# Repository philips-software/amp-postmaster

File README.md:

# Postmaster (Programmer Of ST Microcontrollers Attached to ST Experiment boaRds)

<!-- markdownlint-disable -->

<!-- markdownlint enable -->

## Overview

Postmaster is a device that clicks on top of an STM32 Nucleo-F767ZI board from ST Microelectronics, and through its Ethernet connector you can program the Nucleo and communicate with it.

In this way, Postmaster is usable in hardware-in-the-loop tests, where a test board is reachable through the internet. That test board can first be programmed with the correct firmware. For communicating with the test board, a client can connect to Postmaster via a websocket connection, and talk to the attached board either via a plain UART connection, or via an [ECHO](https://philips-software.github.io/amp-embedded-infra-lib/embedded_infrastructure_library/7.0.0/Echo.html) connection. This communication line is used to execute tests.

Test boards enabled by Postmaster are intended to be inherently scalable; Adding tests boards in a setup should be as simple as putting a Postmaster on top of it, configuring the Postmaster with a few labels describing the characteristics of that board, and connecting it to the internet. A locally installed proxy (also part of this archive) provides discoverability of all Postmasters in its vicinity, and routes incoming requests for boards with certain characteristics to any available board.

By providing a schematics and PCB layout, the Postmaster firmware, and various tools, this repository aims to provide a full suite of components tackling all aspects of connecting a hardware-in-the-loop test board to the cloud.

Requirements of Postmaster are documented [here](Documents/Requirements.md).

## Community

This project uses the [CODE_OF_CONDUCT](./CODE_OF_CONDUCT.md) to define expected conduct in our community. Instances of abusive, harassing, or otherwise unacceptable behavior may be reported by contacting a project [CODEOWNER](.github/CODEOWNERS)

## Changelog

See [CHANGELOG](./CHANGELOG.md) for more info on what's been changed.

## Build

The Postmaster binaries can be built by executing the following commands:

```shell
cmake --preset stm32f407
cmake --build --preset stm32f407-MinSizeRel
```

The postmaster.flex utility can be build by executing the following commands:

```shell
cmake --preset host
cmake --build --preset host-RelWithDebInfo
```

## Reporting vulnerabilities

If you find a vulnerability, please report it to us!
See [security](.github/SECURITY.md) for more information.

## Licenses

See [LICENSE](./LICENSE.md)

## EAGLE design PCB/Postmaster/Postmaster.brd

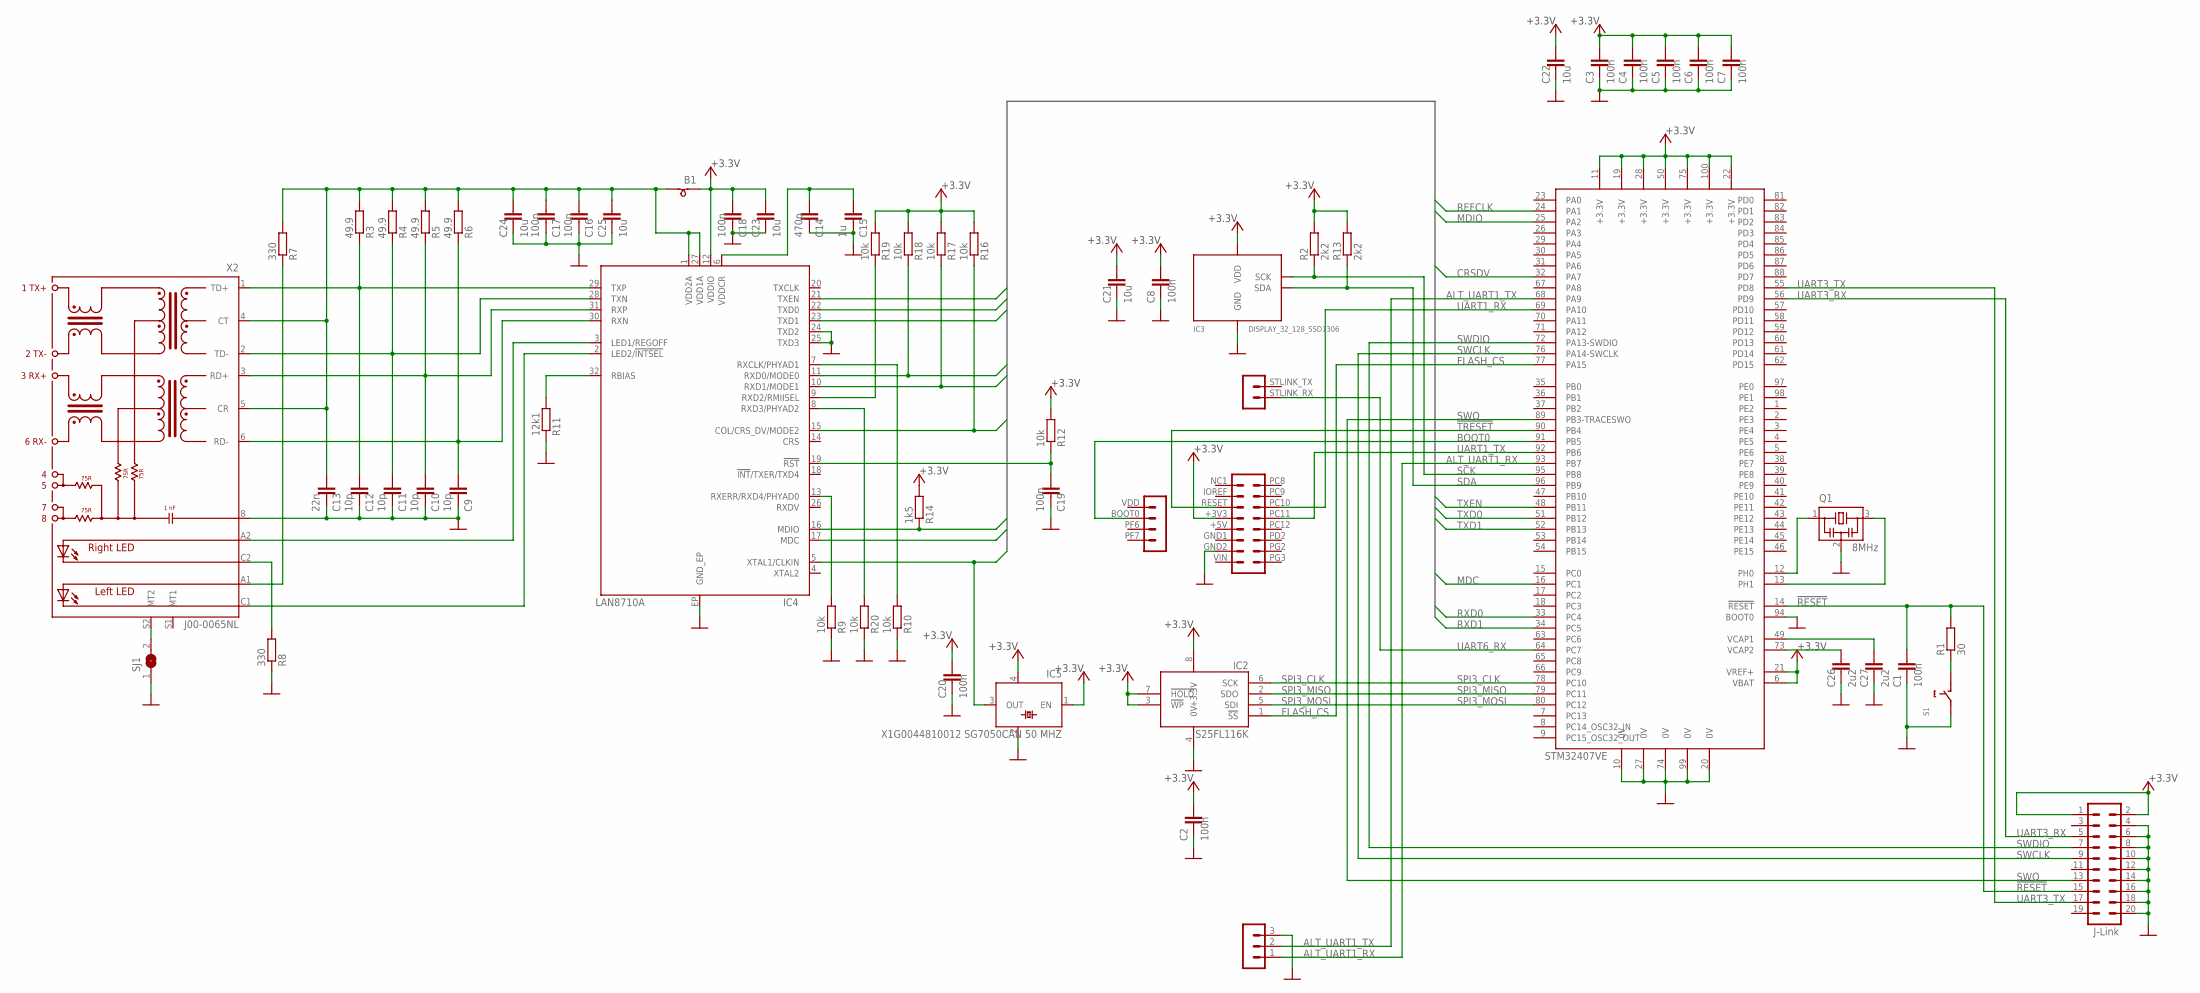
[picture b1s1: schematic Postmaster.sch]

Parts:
B1: BEADSMD; 0805
C1, C2, C3, C4, C5, C6, C7, C8, C16, C17, C18, C19, C20: 100n; 0805
C9, C10, C11, C12: 10p; 0805
C13: 22n; 0805
C14: 470p; 0805
C15: 1u; 0805
C21, C22, C23, C24, C25: 10u; 0805
C26, C27: 2u2; 0805
IC1: STM32F407; TQFP100
IC2: S25FL116K; SOIC8-WIDE
IC3: DISPLAY_32_128_SSD1306; DISPLAY_128_32_SSD1306
IC4: LAN8710A; QFN32
IC5: X1G0044810012 SG7050CAN 50 MHZ; SM77H
Q1: 8MHz; RESONATOR-SMALL
R1: 30; 0805
R2, R13: 2k2; 0805
R3, R4, R5, R6: 49.9; 0805
R7, R8: 330; 0805
R9, R10, R12, R16, R17, R18, R19, R20: 10k; 0805
R11: 12k1; 0805
R14: 1k5; 0805
S1: SWITCHSMD; SWITCH-SMD
SJ1: SJ
U$1: NUCLEO-TOPLEFT
U$3: HEADER-MALE-3
X1: HEADER-IDC-10-2; IDC-10_2
X2: J00-0065NL; ETHERNET

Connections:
0V: C1.2, C2.2, C3.2, C4.2, C5.2, C6.2, C7.2, C8.2, C9.2, C10.2, C11.2, C12.2, C13.2, C14.2, C15.2, C16.2, C17.2, C18.2, C19.2, C20.2, C21.2, C22.2, C23.2, C24.2, C25.2, C26.2, C27.2, IC1.10 (0V), IC1.20 (0V), IC1.27 (0V), IC1.74 (0V), IC1.94 (BOOT0), IC1.99 (0V), IC2.4 (0V), IC3.GND, IC4.24 (TXD2), IC4.25 (TXD3), IC4.EP (GND_EP), IC5.2 (0V), Q1.2, R8.1, R9.1, R10.1, R11.1, R20.1, S1.3 (2), S1.4 (2), SJ1.1, U$1.GND2 (13), U$3.3, X1.4, X1.6, X1.8, X1.10, X1.12, X1.14, X1.16, X1.18, X1.20, X2.8
!RESET!: C1.1, IC1.14 (!RESET!), R1.2, X1.15
!TRESET!: IC1.90 (PB4), U$1.RESET (5)
+3.3V: B1.1, C2.1, C3.1, C4.1, C5.1, C6.1, C7.1, C8.1, C18.1, C20.1, C21.1, C22.1, C23.1, IC1.6 (VBAT), IC1.11 (+3.3V), IC1.19 (+3.3V), IC1.21 (VREF+), IC1.22 (+3.3V), IC1.28 (+3.3V), IC1.50 (+3.3V), IC1.75 (+3.3V), IC1.100 (+3.3V), IC2.3 (!WP!), IC2.7 (!HOLD!), IC2.8 (+3.3V), IC3.VCC (VDD), IC4.12 (VDDIO), IC5.1 (EN), IC5.4 (+3.3V), R2.2, R12.2, R13.2, R14.2, R16.2, R17.2, R18.2, R19.2, U$1.+3V3 (7), X1.1, X1.2
ALT_UART1_RX: IC1.93 (PB7), U$3.1
ALT_UART1_TX: IC1.68 (PA9), U$3.2
BOOT0: IC1.91 (PB5), U$1.BOOT0 (2)
CRSDV: IC1.32 (PA7), IC4.15 (COL/CRS_DV/MODE2), R16.1
FLASH_CS: IC1.77 (PA15), IC2.1 (!SS!)
MDC: IC1.16 (PC1), IC4.17 (MDC)
MDIO: IC1.25 (PA2), IC4.16 (MDIO), R14.1
unnamed: C26.1, IC1.73 (VCAP2)
unnamed: R1.1, S1.1, S1.2 (1)
unnamed: C27.1, IC1.49 (VCAP1)
unnamed: R7.1, X2.A1 (A-L)
unnamed: IC4.3 (LED1/REGOFF), X2.A2 (A-R)
unnamed: R8.2, X2.C2 (C-R)
unnamed: IC1.12 (PH0), Q1.1
unnamed: IC1.13 (PH1), Q1.3
unnamed: C12.1, IC4.29 (TXP), R3.1, X2.1 (TD+)
unnamed: C11.1, IC4.28 (TXN), R4.1, X2.2 (TD-)
unnamed: C10.1, IC4.31 (RXP), R5.1, X2.3 (RD+)
unnamed: C9.1, IC4.30 (RXN), R6.1, X2.6 (RD-)
unnamed: IC4.2 (LED2/!INTSEL!), X2.C1 (C-L)
unnamed: IC4.13 (RXERR/RXD4/PHYAD0), R9.2
unnamed: IC4.7 (RXCLK/PHYAD1), R10.2
unnamed: IC4.32 (RBIAS), R11.2
unnamed: C14.1, C15.1, IC4.6 (VDDCR)
unnamed: SJ1.2, X2.S2 (MT2)
unnamed: B1.2, C13.1, C16.1, C17.1, C24.1, C25.1, IC4.1 (VDD2A), IC4.27 (VDD1A), R3.2, R4.2, R5.2, R6.2, R7.2, X2.4 (CT), X2.5 (CR)
unnamed: C19.1, IC4.19 (!RST!), R12.1
unnamed: IC4.8 (RXD3/PHYAD2), R20.2
unnamed: IC4.9 (RXD2/RMIISEL), R19.1
REFCLK: IC1.24 (PA1), IC4.5 (XTAL1/CLKIN), IC5.3 (OUT)
RXD0: IC1.33 (PC4), IC4.11 (RXD0/MODE0), R18.1
RXD1: IC1.34 (PC5), IC4.10 (RXD1/MODE1), R17.1
SCK: IC1.95 (PB8), IC3.SCK, R2.1
SDA: IC1.96 (PB9), IC3.SDA, R13.1
SPI3_CLK: IC1.78 (PC10), IC2.6 (SCK)
SPI3_MISO: IC1.79 (PC11), IC2.2 (SDO)
SPI3_MOSI: IC1.80 (PC12), IC2.5 (SDI)
SWCLK: IC1.76 (PA14-SWCLK), X1.9
SWDIO: IC1.72 (PA13-SWDIO), X1.7
SWO: IC1.89 (PB3-TRACESWO), X1.13
TXD0: IC1.51 (PB12), IC4.22 (TXD0)
TXD1: IC1.52 (PB13), IC4.23 (TXD1)
TXEN: IC1.48 (PB11), IC4.21 (TXEN)
UART1_RX: IC1.69 (PA10), U$1.PC10 (6)
UART1_TX: IC1.92 (PB6), U$1.PC11 (8)
UART3_RX: IC1.56 (PD9), X1.5
UART3_TX: IC1.55 (PD8), X1.17
UART6_RX: IC1.64 (PC7), U$1.STLINK_RX (1)

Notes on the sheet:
J-Link
STM32407VE

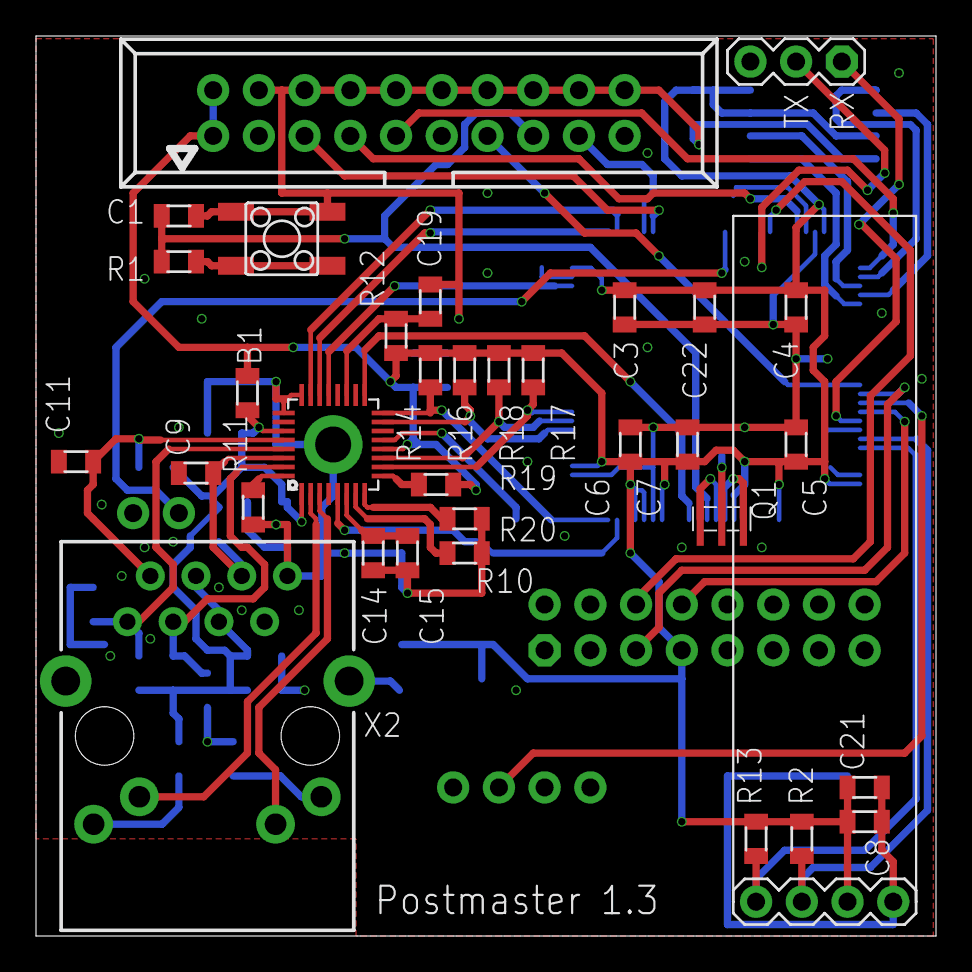
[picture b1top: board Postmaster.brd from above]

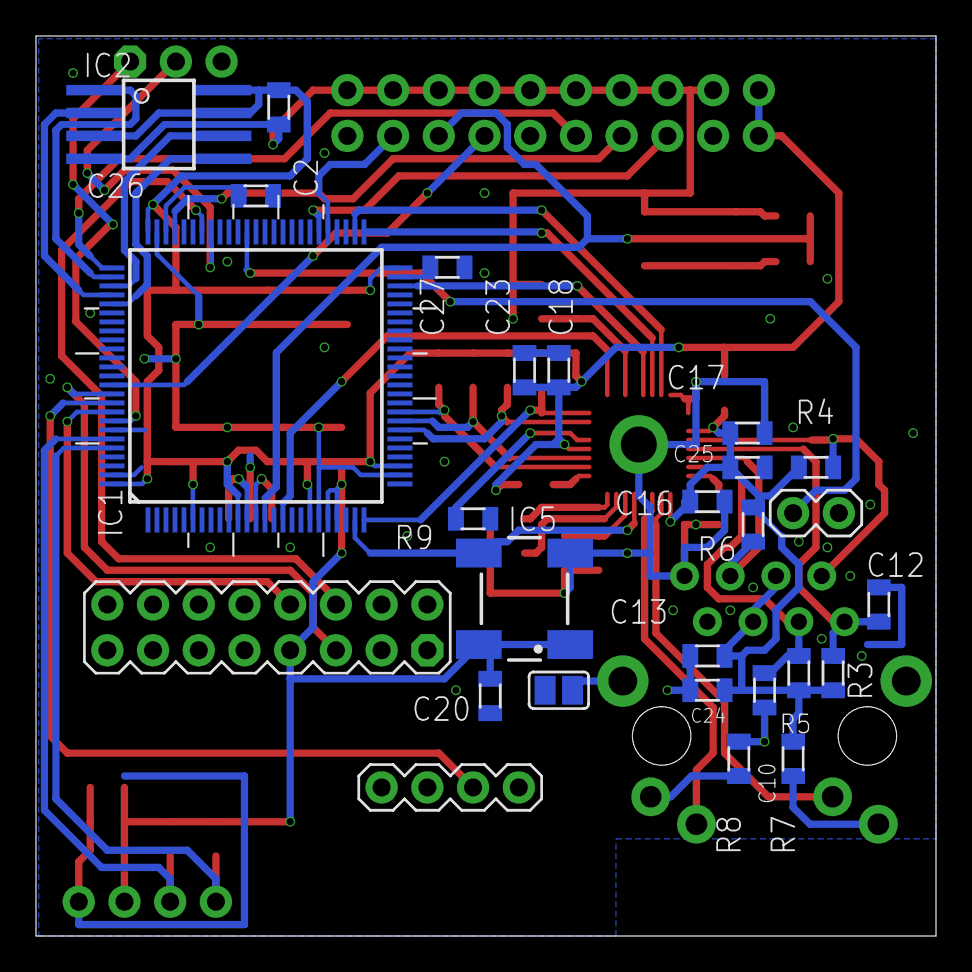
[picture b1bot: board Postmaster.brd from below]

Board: 2 copper layers, 50.0 x 50.0 mm, 59 parts (25 on the bottom side), 52 nets.

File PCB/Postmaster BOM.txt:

Partlist exported from C:/Dev/Postmaster/PCB/Postmaster/Postmaster.sch at 17/04/2022 20:07:00

Part Value                          Device                 Package                Description                
B1   BEADSMD                        BEADSMD                0805                                              
C1   100n                           CAPACITOR0805          0805                                              
C2   100n                           CAPACITOR0805          0805                                              
C3   100n                           CAPACITOR0805          0805                                              
C4   100n                           CAPACITOR0805          0805                                              
C5   100n                           CAPACITOR0805          0805                                              
C6   100n                           CAPACITOR0805          0805                                              
C7   100n                           CAPACITOR0805          0805                                              
C8   100n                           CAPACITOR0805          0805                                              
C9   10p                            CAPACITOR0805          0805                                              
C10  10p                            CAPACITOR0805          0805                                              
C11  10p                            CAPACITOR0805          0805                                              
C12  10p                            CAPACITOR0805          0805                                              
C13  22n                            CAPACITOR0805          0805                                              
C14  470p                           CAPACITOR0805          0805                                              
C15  1u                             CAPACITOR0805          0805                                              
C16  100n                           CAPACITOR0805          0805                                              
C17  100n                           CAPACITOR0805          0805                                              
C18  100n                           CAPACITOR0805          0805                                              
C19  100n                           CAPACITOR0805          0805                                              
C20  100n                           CAPACITOR0805          0805                                              
C21  10u                            CAPACITOR0805          0805                                              
C22  10u                            CAPACITOR0805          0805                                              
C23  10u                            CAPACITOR0805          0805                                              
C24  10u                            CAPACITOR0805          0805                                              
C25  10u                            CAPACITOR0805          0805                                              
C26  2u2                            CAPACITOR0805          0805                                              
C27  2u2                            CAPACITOR0805          0805                                              
IC1  STM32F407                      STM32F407              TQFP100                                           
IC2  S25FL116K                      S25FL116KW             SOIC8-WIDE                                        
IC3  DISPLAY_32_128_SSD1306         DISPLAY_32_128_SSD1306 DISPLAY_128_32_SSD1306                            
IC4  LAN8710A                       LAN8710A               QFN32                                             
IC5  X1G0044810012 SG7050CAN 50 MHZ SM77H                  SM77H                  3.3V CMOS Clock Oscillator 
Q1   8MHz                           RESONATOR-S            RESONATOR-SMALL                                   
R1   30                             RESISTORR0805          0805                                              
R2   2k2                            RESISTORR0805          0805                                              
R3   49.9                           RESISTORR0805          0805                                              
R4   49.9                           RESISTORR0805          0805                                              
R5   49.9                           RESISTORR0805          0805                                              
R6   49.9                           RESISTORR0805          0805                                              
R7   330                            RESISTORR0805          0805                                              
R8   330                            RESISTORR0805          0805                                              
R9   10k                            RESISTORR0805          0805                                              
R10  10k                            RESISTORR0805          0805                                              
R11  12k1                           RESISTORR0805          0805                                              
R12  10k                            RESISTORR0805          0805                                              
R13  2k2                            RESISTORR0805          0805                                              
R14  1k5                            RESISTORR0805          0805                                              
R16  10k                            RESISTORR0805          0805                                              
R17  10k                            RESISTORR0805          0805                                              
R18  10k                            RESISTORR0805          0805                                              
R19  10k                            RESISTORR0805          0805                                              
R20  10k                            RESISTORR0805          0805                                              
S1   SWITCHSMD                      SWITCHSMD              SWITCH-SMD                                        
SJ1                                 SJ                     SJ                     SMD solder JUMPER          
U$1  NUCLEO-TOPLEFT                 NUCLEO-TOPLEFT         NUCLEO-TOPLEFT                                    
X1   HEADER-IDC-10-2                HEADER-IDC-10-2        IDC-10_2                                          
X2   J00-0065NL                     J00-0065NL             ETHERNET

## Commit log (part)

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2024-12-04 Update submodules
2024-12-04 ci: validate pull request titles
2024-12-06 feat(deps): bump the git-submodules group with 2 updates
    Bumps the git-submodules group with 2 updates: [amp-embedded-infra-lib](https://github.com/philips-software/amp-embedded-infra-lib) and [amp-hal-st](https://github.com/philips-software/amp-hal-st).
    Updates `amp-embedded-infra-lib` from `6c84af5` to `c77731b`
    - [Release notes](https://github.com/philips-software/amp-embedded-infra-lib/releases)
    - [Commits](https://github.com/philips-software/amp-embedded-infra-lib/compare/6c84af5324c79219059d1066cc5ce3aad8f2b927...c77731ba79bfbe8af22450cf33fcdf4fd30a3587)
    Updates `amp-hal-st` from `1529067` to `f11d3bf`
    - [Release notes](https://github.com/philips-software/amp-hal-st/releases)
2024-12-19 postmaster/flex/Main: Fix reading from environment
2025-01-10 feat(deps): bump the git-submodules group across 1 directory with 3 updates
    Bumps the git-submodules group with 3 updates in the / directory: [amp-embedded-infra-lib](https://github.com/philips-software/amp-embedded-infra-lib), [amp-hal-st](https://github.com/philips-softwar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
    Updates `amp-embedded-infra-lib` from `6c84af5` to `ae01eea`
    - [Release notes](https://github.com/philips-software/amp-embedded-infra-lib/releases)
    - [Commits](https://github.com/philips-software/amp-embedded-infra-lib/compare/6c84af5324c79219059d1066cc5ce3aad8f2b927...ae01eeae459647a0f8a52430bb26740d47b2945e)
    Updates `amp-hal-st` from `1
2025-01-19 Accept multiple connections on port 80, one connection on port 8080
2025-01-31 build(deps): bump the github-actions group across 1 directory with 6 updates
    Bumps the github-actions group with 6 updates in the / directory:
    | Package | From | To |
    | --- | --- | --- |
    | [hendrikmuhs/ccache-action](https://github.com/hendrikmuhs/ccache-action) | `1.2.14` | `1.2.16` |
    | [oxsecurity/megalinter](https://github.com/oxsecurity/megalinter) | `8.3.0` | `8.4.1` |
    | [actions/upload-artifact](https://github.com/actions/upload-artifact) | `4.5.0` | `4.6.0` |
2025-02-13 build(deps): bump philips-software/amp-devcontainer-cpp
    Bumps [philips-software/amp-devcontainer-cpp](https://github.com/philips-software/amp-devcontainer) from v5.6.0 to v5.6.1.
    - [Release notes](https://github.com/philips-software/amp-devcontainer/releases)
    - [Changelog](https://github.com/philips-software/amp-devcontainer/blob/main/CHANGELOG.md)
    - [Commits](https://github.com/philips-software/amp-devcontainer/compare/v5.6.0...v5.6.1)
    ---
    updated-dependencies:
2025-02-20 feat: add kicad design for Postmaster (#51)
    * feat: redo the schematics and board in KiCad
    * Update schematics
    * Update schematics
    * Update schematics
    * Update schematics
    * Update schematics, add production files
2025-03-03 feat(deps): bump the git-submodules group across 1 directory with 3 updates
    Bumps the git-submodules group with 3 updates in the / directory: [amp-embedded-infra-lib](https://github.com/philips-software/amp-embedded-infra-lib), [amp-hal-st](https://github.com/philips-softwar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
    Updates `amp-embedded-infra-lib` from `6c84af5` to `eccbab6`
    - [Release notes](https://github.com/philips-software/amp-embedded-infra-lib/releases)
    - [Commits](https://github.com/philips-software/amp-embedded-infra-lib/compare/6c84af5324c79219059d1066cc5ce3aad8f2b927...eccbab6e47da83929395a27b047a695ecd29e7a6)
    Updates `amp-hal-st` from `1
2025-03-24 build(deps): bump the github-actions group across 1 directory with 6 updates
    Bumps the github-actions group with 6 updates in the / directory:
    | Package | From | To |
    | --- | --- | --- |
    | [actions/cache](https://github.com/actions/cache) | `4.2.1` | `4.2.3` |
    | [oxsecurity/megalinter](https://github.com/oxsecurity/megalinter) | `8.4.2` | `8.5.0` |
    | [actions/upload-artifact](https://github.com/actions/upload-artifact) | `4.6.0` | `4.6.2` |
2025-04-25 build(deps): bump philips-software/amp-devcontainer-cpp
    Bumps [philips-software/amp-devcontainer-cpp](https://github.com/philips-software/amp-devcontainer) from v5.6.2 to v6.0.1.
    - [Release notes](https://github.com/philips-software/amp-devcontainer/releases)
    - [Changelog](https://github.com/philips-software/amp-devcontainer/blob/main/CHANGELOG.md)
    - [Commits](https://github.com/philips-software/amp-devcontainer/compare/v5.6.2...v6.0.1)
    ---
    updated-dependencies:
2025-05-08 build(deps): bump oxsecurity/megalinter in the github-actions group (#78)
    Bumps the github-actions group with 1 update: [oxsecurity/megalinter](https://github.com/oxsecurity/megalinter).
    Updates `oxsecurity/megalinter` from 8.6.0 to 8.7.0
    - [Release notes](https://github.com/oxsecurity/megalinter/releases)
    - [Changelog](https://github.com/oxsecurity/megalinter/blob/main/CHANGELOG.md)
    - [Commits](https://github.com/oxsecurity/megalinter/compare/04cf22b980c2e9c2121553417ed651c944afc8e1...5a91fb06c83d0e69fbd23756d47438aa723b4a5a)
    ---
2025-05-21 chore(deps): bump philips-software/amp-devcontainer-cpp
    Bumps [philips-software/amp-devcontainer-cpp](https://github.com/philips-software/amp-devcontainer) from v6.0.1 to v6.0.2.
    - [Release notes](https://github.com/philips-software/amp-devcontainer/releases)
    - [Changelog](https://github.com/philips-software/amp-devcontainer/blob/main/CHANGELOG.md)
    - [Commits](https://github.com/philips-software/amp-devcontainer/compare/v6.0.1...v6.0.2)
    ---
    updated-dependencies:
2025-05-22 fix: align flash writes to 16 bytes (#80)
    * fix: align flash writes to 16 bytes
    * Wait for flash initialization done
    * FlexHttpClient: Move attaching of websocket
    * FirmwareReceptorResetTarget: Use timers instead of HAL_Delay
    * Set starting
    * Update container
2025-06-16 chore(deps): bump the github-actions group across 1 directory with 6 updates
    Bumps the github-actions group with 6 updates in the / directory:
    | Package | From | To |
    | --- | --- | --- |
    | [actions/checkout](https://github.com/actions/checkout) | `4.1.7` | `4.2.2` |
    | [docker/metadata-action](https://github.com/docker/metadata-action) | `5.5.1` | `5.7.0` |
    | [docker/setup-buildx-action](https://github.com/docker/setup-buildx-action) | `3.6.1` | `3.10.0` |
2025-08-08 chore(deps): bump the github-actions group across 1 directory with 4 updates (#98)
    Bumps the github-actions group with 4 updates in the / directory: [actions/cache](https://github.com/actions/cache), [docker/metadata-action](https://github.com/docker/metadata-action), [docker/login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
    Updates `actions/cache` from 4.2.3 to 4.2.4
    - [Release notes](https://github.com/actions/cache/releases)
    - [Changelog](https://github.com/actions/cache/blob/main/RELEASES.md)
    - [Commits](https://github.com/actions/cache/compare/5a3ec84eff668545956fd18022155c47e9
2025-09-10 chore(deps): bump philips-software/amp-devcontainer-cpp
    Bumps [philips-software/amp-devcontainer-cpp](https://github.com/philips-software/amp-devcontainer) from 6.2.1 to 6.3.0.
    - [Release notes](https://github.com/philips-software/amp-devcontainer/releases)
    - [Changelog](https://github.com/philips-software/amp-devcontainer/blob/main/CHANGELOG.md)
    - [Commits](https://github.com/philips-software/amp-devcontainer/compare/v6.2.1...v6.3.0)
    ---
    updated-dependencies:
2025-10-08 chore(deps): bump philips-software/amp-devcontainer-cpp (#114)
    Bumps [philips-software/amp-devcontainer-cpp](https://github.com/philips-software/amp-devcontainer) from 6.2.1 to v6.5.0.
    - [Release notes](https://github.com/philips-software/amp-devcontainer/releases)
    - [Changelog](https://github.com/philips-software/amp-devcontainer/blob/main/CHANGELOG.md)
    - [Commits](https://github.com/philips-software/amp-devcontainer/compare/v6.2.1...v6.5.0)
    ---
    updated-dependencies:
2025-10-23 chore: enable usb passthrough debugging (#119)
2025-10-27 feat(deps): bump the git-submodules group across 1 directory with 3 updates
    Bumps the git-submodules group with 3 updates in the / directory: [amp-embedded-infra-lib](https://github.com/philips-software/amp-embedded-infra-lib), [amp-hal-st](https://github.com/philips-softwar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
    Updates `amp-embedded-infra-lib` from `9d3718f` to `2c26042`
    - [Release notes](https://github.com/philips-software/amp-embedded-infra-lib/releases)
    - [Commits](https://github.com/philips-software/amp-embedded-infra-lib/compare/9d3718fe966a1b4308b1f7ee4deb572958733cf9...2c260424bb9e220a8ccc9a4ea43ec7154cfd2eb0)
    Updates `amp-hal-st` from `f
2025-11-26 chore(deps): bump philips-software/amp-devcontainer-cpp
    Bumps [philips-software/amp-devcontainer-cpp](https://github.com/philips-software/amp-devcontainer) from v6.5.0 to v6.6.1.
    - [Release notes](https://github.com/philips-software/amp-devcontainer/releases)
    - [Changelog](https://github.com/philips-software/amp-devcontainer/blob/main/CHANGELOG.md)
    - [Commits](https://github.com/philips-software/amp-devcontainer/compare/v6.5.0...v6.6.1)
    ---
    updated-dependencies:
2025-12-16 build: remove MinSizeRel configuration
2025-12-18 Allow containers in linting
2025-12-19 Create installation package
2025-12-19 chore(main): release 0.3.0
2025-12-22 build(deps): bump actions/download-artifact from 6.0.0 to 7.0.0
    Bumps [actions/download-artifact](https://github.com/actions/download-artifact) from 6.0.0 to 7.0.0.
    - [Release notes](https://github.com/actions/download-artifact/releases)
    - [Commits](https://github.com/actions/download-artifact/compare/018cc2cf5baa6db3ef3c5f8a56943fffe632ef53...37930b1c2abaa49bbe596cd826c3c89aef350131)
    ---
    updated-dependencies:
    - dependency-name: actions/download-artifact
2026-01-05 feat(deps): bump the git-submodules group across 1 directory with 3 updates (#153)
    Bumps the git-submodules group with 3 updates in the / directory: [amp-embedded-infra-lib](https://github.com/philips-software/amp-embedded-infra-lib), [amp-hal-st](https://github.com/philips-softwar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
    Updates `amp-embedded-infra-lib` from `7b3044e` to `eda0964`
    - [Release notes](https://github.com/philips-software/amp-embedded-infra-lib/releases)
    - [Commits](https://github.com/philips-software/amp-embedded-infra-lib/compare/7b3044eedcc65598b3f6df89f204d9a69895df39...eda09647446baea1a96017675e09e654c23bee9d)
    Updates `amp-hal-st`
2026-01-05 fix: install postmaster binaries (#146)
    * fix: install postmaster binaries
    * Add map and hex files
    * Create and release upgrade pack
    * Fix character
    * Move Build Upgrade Pack to continuous-integration.yml
    * Fix artifact name
2026-01-06 fix: release version in upg file names
2026-01-06 Fix sed formatting
2026-01-07 Moar quotes
2026-01-08 build(deps): bump docker/setup-buildx-action in the github-actions group
    Bumps the github-actions group with 1 update: [docker/setup-buildx-action](https://github.com/docker/setup-buildx-action).
    Updates `docker/setup-buildx-action` from 3.11.1 to 3.12.0
    - [Release notes](https://github.com/docker/setup-buildx-action/releases)
    - [Commits](https://github.com/docker/setup-buildx-action/compare/e468171a9de216ec08956ac3ada2f0791b6bd435...8d2750c68a42422c14e847fe6c8ac0403b4cbd6f)
    ---
    updated-dependencies:
2026-01-08 Refactor
2026-01-08 chore(main): release 0.5.0 (#166)
2026-02-05 build(deps): bump the github-actions group across 1 directory with 4 updates
    Bumps the github-actions group with 4 updates in the / directory: [step-security/harden-runner](https://github.com/step-security/harden-runner), [docker/login-action](https://github.com/docker/login-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
    Updates `step-security/harden-runner` from 2.14.0 to 2.14.1
    - [Release notes](https://github.com/step-security/harden-runner/releases)
    - [Commits](https://github.com/step-security/harden-runner/compare/20cf305ff2072d973412fa9b1e3a4f227bda3c76...e3f713f2d8f53843e71c69a996d56f51aa9adfb9)
2026-03-06 build(deps): bump the github-actions group across 1 directory with 3 updates
    Bumps the github-actions group with 3 updates in the / directory: [actions/checkout](https://github.com/actions/checkout), [zizmorcore/zizmor-action](https://github.com/zizmorcore/zizmor-action) and 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
    Updates `actions/checkout` from 6.0.1 to 6.0.2
    - [Release notes](https://github.com/actions/checkout/releases)
    - [Changelog](https://github.com/actions/checkout/blob/main/CHANGELOG.md)
    - [Commits](https://github.com/actions/checkout/compare/8e8c483db84b4bee98b60c0593521ed34d9990e8...de0fac2e4500dabe0009e67214ff5f5447ce83dd)
    Updates `zizmorcore/zizmor-action` from 0.3.
